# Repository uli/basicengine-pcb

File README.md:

#  BASIC Engine PCB

The BASIC Engine is a very low-cost single-board home computer with advanced 
2D color graphics and sound capabilities, roughly comparable to late-1980s
or early-1990s computers and video game consoles.  It can be built at home
without special skills or tools and using readily available components for
under 10 Euros in parts, or mass-produced for even less.

This repository contains KiCAD schematics and the PCB layout. Gerber files
for ordering PCBs can be found in the [release section](https://github.com/uli/basicengine-pcb/releases).

Software can be found in the [BASIC Engine firmware](https://github.com/uli/basicengine-firmware)
repository.

## Hardware features

- ESP12-E/F module with ESP8266 SoC and 4 MB flash memory
- VS23S010 video controller with 128k RAM and composite video output in PAL or NTSC
- 5-bit PCM sound from I2S controller
- MicroSD card slot
- PS/2 and PS/2-compatible USB keyboard interface
- PlayStation controller port
- PCF8575 I/O extender with 16 GPIO pins
- I2C and SPI busses on I/O expansion connector
- power supplied via Micro-USB socket or pin header
- RCA connectors for video and audio

## Components

The BASIC Engine does not use any obsolete components that may be difficult
to obtain.  Nevertheless, you will have to put in at least three orders to
get all required parts.

I would recommend to get the circuit board from JLCPCB or Smart Prototyping,
the VS23S010D-L chip from TME, and all other parts from AliExpress.  AE
usually has the lowest price, and this project is all about the cheap.

You will usually have to order more components than you actually intend to
use, because
- they are only offered in larger quantities,
- you may want to save on shipping in case you decide to build more BASIC Engines,
- you are likely to break or lose a few parts while building the device, or
- all of the above.

**Note:** Unless noted otherwise, all links lead to suppliers and components
I have bought myself in the past and that have received the "Good Enough for
BASIC Engine" seal of approval.  Nevertheless you **order at your own
risk**, and I cannot be held responsible for the quality of the services or
products provided to you.  I am not affiliated with any of the linked
suppliers.

### Required components

|Qty	|Name				|Package|Where to get it					|Links|
|-------|-------------------------------|-------|-------------------------------------------------------|-----|
|1	|Circuit Board			|	|Any board house					|[JLCPCB](https://jlcpcb.com/quote), [Smart Prototyping](https://www.smart-prototyping.com/PCB-Prototyping.html).
|1	|VS23S010D-L video controller	|	|TME (small quantities), VLSI (for large orders)	|[TME](https://www.tme.eu/en/details/vs23s010d-l/parallel-sram-memories-integ-circ/vlsi/), [VLSI](https://webstore.vlsi.fi/epages/vlsi.sf/en_GB/?ObjectPath=/Shops/2015020901/Categories/%22Circuits%20and%20KITs%22/VS23S010)
|1	|ESP-12F or ESP-12E microcontroller module|	|AliExpress, eBay, Amazon, various smaller retailers	|AliExpress: [1](https://www.aliexpress.com/item/New-version-ESP-12E-replace-ESP-12-ESP8266-remote-serial-Port-WIFI-wireless-module/32339917567.html), [2](https://www.aliexpress.com/item/1PCS-ESP-12F-ESP-12E-upgrade-ESP8266-Remote-Serial-Port-WIFI-Wireless-Module-ESP8266-4M-Flash/32521015580.html), [3](https://www.aliexpress.com/item/1PCS-ESP-12F-ESP-12E-upgrade-ESP8266-Remote-Serial-Port-WIFI-Wireless-Module-ESP8266-4M-Flash/32521015580.html)
|8	|Resistor 10K			|1206	|Generic part						|AliExpress: [1](https://www.aliexpress.com/item/500pcs-1206-SMD-Resistor-1-10K-ohm-chip-resistor-0-25W-1-4W-103/32806664929.html), [2](https://www.aliexpress.com/item/1206-10K-ohm-5-1-4W-Resistor-3216-103-Chip-resistor-500Pcs-Lot/32601535320.html)
|1	|Resistor 1M			|1206	|Generic part						|AliExpress: [1](https://www.aliexpress.com/item/500pcs-1206-SMD-Resistor-1-1M-ohm-chip-resistor-0-25W-1-4W-106/32806720513.html)
|1	|Resistor 75 Ohms		|1206	|Generic part						|AliExpress: [1](https://www.aliexpress.com/item/100pcs-lot-1206-5-75-ohm-75R-750-1-4W-0-25W-SMD-Resistor-3-2/32681304598.html), [2 (untested supplier)](https://www.aliexpress.com/item/200pcs-lot-SMD-Chip-Resistor-1206-68R-75R-82R-91R-100R-5-Resistance-68-75-82/32830700367.html)
|2	|Resistor 1K			|1206	|Generic part						|AliExpress: [1](https://www.aliexpress.com/item/500pcs-1206-SMD-Resistor-1-1K-ohm-chip-resistor-0-25W-1-4W-102/32806736163.html)
|8	|Capacitor 100nF		|1206	|Generic part						|AliExpress: [1](https://www.aliexpress.com/item/100pcs-100NF-X7R-Error-10-50V-0-1UF-104-1206-smd-capacitor/32810080501.html), [2](https://www.aliexpress.com/item/100PCS-SMD-chip-Ceramic-capacitors-1206-104-100NF-0-1UF-1206-Y5V/1478483210.html), [3](https://www.aliexpress.com/item/100PCS-1206-104-100NF-0-1UF-1206-SMD-capacitance/32836586837.html), [4](https://www.aliexpress.com/item/Free-Shipping-100PCS-1206-104-100NF-0-1UF-1206-SMD-capacitance/1096160798.html)
|2	|Capacitor 56pF			|1206	|Generic part						|AliExpress: [1](https://www.aliexpress.com/item/100pcs-1206-smd-capacitor-25pF-27pF-30pF-33pF-36pF-39pF-47pF-51pF-56pF-68pF/32832398866.html)
|1	|Electrolytic capacitor 10uF (**Revision 1 board only!**)	|THT	|Generic part		|AliExpress: [1](https://www.aliexpress.com/item/Free-shiiping-50pcs-Aluminum-electrolytic-capacitor-10uF-50V-5-7-Electrolytic-capacitor/32326606304.html), [2](https://www.aliexpress.com/item/50-pcs-Electrolytic-Capacitors-50V-10UF-4X7MM-Aluminum-Electrolytic-Capacitor/1808204181.html)
|2	|Electrolytic Capacitor 220uF (**Revision 1 board only!**)	|THT	|Generic part		|AliExpress: [1](https://www.aliexpress.com/item/1LOT-50PCS-Aluminum-Capacitors-220uF-227-20-6-11mm-25V-220000nF-220000000pF-Diameter6mm/32707926097.html)
|1	|Capacitor 10uF (**Revision 2 board only!**)|1206	|Generic part				|AliExpress: [1](https://www.aliexpress.com/item/Free-Shopping-100PCS-smd-ceramic-capacitor-1206-3216-10uf-106-25V-10/870636274.html), [2](https://www.aliexpress.com/store/product/100PCS-LOT-10uf-Error-10-50V-106-10UF-1206-SMD-Thick-Film-Chip-Multilayer-Ceramic-Capacitor/1815642_32818359105.html)
|2	|Capacitor 22uF (**Revision 2 board only!**)|1206	|Generic part				|AliExpress: [1](https://www.aliexpress.com/item/1206-22UF-226M-Y5V-10V-SMD-Chip-Multilayer-Ceramic-Capacitor-Capacitor/32506900002.html), [2](https://www.aliexpress.com/item/100PCS-LOT-22uf-Error-10-50V-226-22UF-1206-SMD-Thick-Film-Chip-Multilayer-Ceramic-Capacitor/32818355106.html)
|2	|RCA connectors			|THT	|Generic, but often overpriced part			|AliExpress: [1 (untested supplier)](https://www.aliexpress.com/item/ROHS-high-quality-one-pin-rca-jack-connector-RCA-103P/32305697673.html); no longer available: [red](https://www.aliexpress.com/item/10-Pcs-Pcb-Mount-3-Pin-Av-Concentric-Outlet-1-Rca-Female-Socket-Board-Connector/32778665156.html), [yellow](https://www.aliexpress.com/item/20-Pcs-3P-Pcb-Mounting-Yellow-1-Rca-Female-Outlet-Jack-Audio-Video-Av-Connector/32773151735.html)
|1	|Micro-USB connector		|SMT	|Generic, but often overpriced part			|AliExpress: [1](https://www.aliexpress.com/item/10Pcs-Micro-USB-5P-5-pin-Micro-USB-Jack-5Pins-No-Curling-Micro-USB-Connector-Tail/32697562974.html), [2](https://www.aliexpress.com/item/10pcs-LOT-Micro-USB-5P-5-pin-Micro-USB-Jack-5Pins-Micro-USB-Connector-Tail-Charging/32482316889.html), [3](https://www.aliexpress.com/item/10pcs-G21-Micro-USB-5pin-DIP-Female-Connector-For-Mobile-Phone-Mini-USB-Charging-Socket-Curly/32739335401.html), [4](https://www.aliexpress.com/item/50pcs-Lot-Micro-USB-5pin-B-type-Female-Connector-For-Mobile-Phone-Micro-USB-Jack-Connector/32740232877.html)
|1	|Regulator AMS1117 3.3V		|SOT-223|Generic, sometimes overpriced part			|AliExpress: [1](https://www.aliexpress.com/item/10pcs-AMS1117-3-3-AMS1117-LM1117-1117-3-3V-1A-Voltage-Regulator/32348815272.html); eBay DE: [1](https://www.ebay.de/itm/50-Stueck-AMS1117-3-3-Niedrig-Aussetzer-Spannungsregler-3-3V-1A-SOT-223-GY-/262752156305?hash=item3d2d3fba91)
|1	|74HC04 hex inverter		|SOIC-14|Generic part						|AliExpress: [1](https://www.aliexpress.com/item/20PCS-74HC04D-SOP14-74HC04-SOP-SN74HC04DR-SMD-new-and-original-IC-free-shipping/32545540311.html), [2](https://www.aliexpress.com/item/20PCS-74HC04-SOP/32833871593.html)
|1	|Crystal 3.579545 MHz (NTSC) or 4.433619 MHz (PAL)|HC49-S	|Generic part				|AliExpress: [NTSC](https://www.aliexpress.com/item/10pcs-lot-Crystal-Oscillator-3-579545MHz-3-579545-MHz3-579545M-Hz-3-579545M-Mini-Passive-Resonator/32674141136.html), [PAL (untested supplier)](https://www.aliexpress.com/item/4-433MHZ-4-433M-HC-49S-Quartz-crystal-4-433Mhz-4-433m-DIP-Quartz-crystal-resonators/897579150.html)
|1	|PS/2 keyboard connector (female)|THT	|AliExpress, some distributors				|AliExpress: [green](https://www.aliexpress.com/item/20PCS-Lot-PS2-Green-Plug-Jack-Socket-Connector-6Pin-for-keyboard-mouse/32502046263.html), [purple](https://www.aliexpress.com/item/20PCS-Lot-PS2-Purple-Plug-Jack-Socket-Connector-6P-6Pin-for-keyboard-mouse/32503500361.html)

### Not strictly required, but strongly recommended components

|Qty	|Name				|Package|Who can supply it					|Links|
|-------|-------------------------------|-------|-------------------------------------------------------|-----|
|1	|Pin header 1x7 (programming header)|	|Generic part						|AliExpress: [1](https://www.aliexpress.com/item/1-pcs-color-2-54mm-Black-White-Red-Yellow-Blue-Green-1X40-Single-Row-Pin-Male/32776690848.html) (1x40 headers, cut them to size)
|1	|MicroSD socket			|SMT	|AliExpress, eBay					|AliExpress: [1](https://www.aliexpress.com/item/10pcs-MicroSD-Card-socket-connector-pop-up/1878206296.html), [2](https://www.aliexpress.com/item/Free-Shipping-10PCS-MicroSD-Card-socket-connector-pop-up/1688131297.html); eBay DE: [1](https://www.ebay.de/itm/10Pcs-TransFlash-SD-TF-Micro-Memory-Card-Self-eject-Socket-Adapter-Plug-NEW-/272247684402?hash=item3f6339fd32)
|1	|Push button 6x6x4.3 mm		|THT	|Generic part						|AliExpress: [1](https://www.aliexpress.com/item/10PCS-TC-1212T-6x6x4-3-mm-Tact-Tactile-Push-Button-Momentary-SMD-PCB-Switch/32633194631.html), [2](https://www.aliexpress.com/item/20PCS-6X6X4-3-DIP-vertical-Tactile-Tact-Push-Button-Switch-Micro-Switch-Momentary-6-6-4/32628754816.html)
|1	|PCF8575TS I2C I/O extender	|SSOP-24|Generic part; AliExpress recommended for price		|AliExpress: [1](https://www.aliexpress.com/item/5PCS-PCF8575TS-SSOP24-PCF8575-SOP24/32836090166.html)
|1	|Raspberry Pi 3 case		|	|Generic part						|AliExpress: [1](https://www.aliexpress.com/item/case-H1-Black-Raspberry-PI-3-model-B-Case-Cover-Shell-Enclosure-ABS-Plastic-Box-for/32813179636.html), [2](https://www.aliexpress.com/item/box-F3-for-Raspberry-PI-3-model-B-Transparent-Green-Case-Cover-Shell-Enclosure-Box/32824924648.html), [3](https://www.aliexpress.com/item/10pcs-lot-Raspberry-Pi-3-case-Official-ABS-enclosure/32816503175.html), [4](https://www.aliexpress.com/item/New-Arrival-Raspberry-Pi-3-Model-B-Case-Black-Red-ABS-Plastic-Box-Closed-Cover-Shell/32716194619.html), [5](https://www.aliexpress.com/item/Raspberry-Pi-3-Model-B-ABS-Case-Black-White-Tranparent-ABS-Enclosure-Box-Shell-for-Raspberry/32651704900.html)

### Optional components

|Qty	|Name				|Package|Who can supply it					|Links|
|-------|-------------------------------|-------|-------------------------------------------------------|-----|
|1	|Pin header 1x3 pins (alternative power supply)|	|AliExpress recommended for price	|see "Pin header 1x7"
|1	|USB A connector (alternative keyboard connector)|THT	|Generic part				|AliExpress: [1](https://www.aliexpress.com/item/10-PCS-USB-Type-A-Female-PCB-Mount-Socket-Plug-Connector-Right-Angle-4-Pin-New/32821630374.html), [2](https://www.aliexpress.com/item/10PCS-USB-type-A-USB-mother-Curved-needle/32265708803.html)
|1	|Pin header 2x20 pins (expansion connector)|	|AliExpress recommended for price		|AliExpress: [1](https://www.aliexpress.com/item/30-pcs-set-2-54mm-Black-White-Red-Yellow-Blue-Green-2X40-Double-Row-Pin-Male/32776804458.html) (2x40 headers, cut them in half)
|1	|PlayStation controller connector (female)|	|AliExpress					|AliExpress: [1](https://www.aliexpress.com/item/10pcs-wholesale-Replacement-9-Pin-Female-Connector-Game-Controller-Socket-Slot-for-PS2-Console-for-playstation/32769355434.html), [2](https://www.aliexpress.com/item/10pcs-Replacement-9-Pin-90-degrees-Female-Connector-Game-Controller-Socket-Slot-for-PS2-Console/32818887920.html)

### Programming tools

Used to flash the firmware into the microcontroller module. You only need one set of these.

|Qty	|Name				|Package|Who can supply it				|Links|
|-------|-------------------------------|-------|-----------------------------------------------|-----|
|1	|USB-to-serial converter	|	|AliExpress, eBay				|AliExpress: [1](https://www.aliexpress.com/item/1pcs-FT232RL-FTDI-USB-3-3V-5-5V-to-TTL-Serial-Adapter-Module-forArduino-Mini-Port/32650148276.html), [2](https://www.aliexpress.com/item/CP2102-USB-2-0-to-TTL-UART-Module-6Pin-Serial-Converter-STC-Replace-FT232-Module/32279672853.html)
|7	|Dupont wires female/female (for wiring the converter to the programming header)|	|AliExpress, eBay	|AliExpress: [1 (untested supplier)](https://www.aliexpress.com/item/40pcs-dupont-cable-jumper-wire-dupont-line-female-to-female-dupont-line-20cm-1P-40P-free/32848338475.html), [2 (untested supplier)](https://www.aliexpress.com/item/40pcs-dupont-cable-jumper-wire-dupont-line-female-to-female-dupont-line-20cm-1P-1P-for/32586620163.html)

## Ordering the PCB

If you have never had a custom circuit board made, you may find the
multitude of options you are presented with on the board house's ordering
page confusing.  The good news is that you do not have to worry about most
of them, because they have been set to reasonable defaults already.  If you
order with JLCPCB or Smart Prototyping using the links above, all you have
to do is upload the ZIP file containing the Gerber files that you can find
in the [release section](https://github.com/uli/basicengine-pcb/releases)
and specify the dimensions of the board (85x56 mm).  All other options can
be left as is.

(Just to be on safe side: At the time of writing these options were: 2
layers, 1.6 mm thickness, HASL with lead, 1oz copper weight, material FR4.)

## Assembling the BASIC Engine

Even though it uses some small-pitch components, the BASIC Engine has been
designed to be easy to assemble.

Click on the thumbnail below to watch a one-hour silent video showing how to
build it using a soldering iron, a heat gun, tweezers,
solder wire and side cutters, without fancy tools, mad soldering skills and
with only a minimal amount of patience:

## PCB Errata

Revision 2 of the PCB contains one error:

- R6 value is given as "22R", should be "75R".

Revision 1 of the PCB contains two errors:

- R6 value is given as "22R", should be "75R".
- C3 and C4 values are given as "10p", should be "56p".

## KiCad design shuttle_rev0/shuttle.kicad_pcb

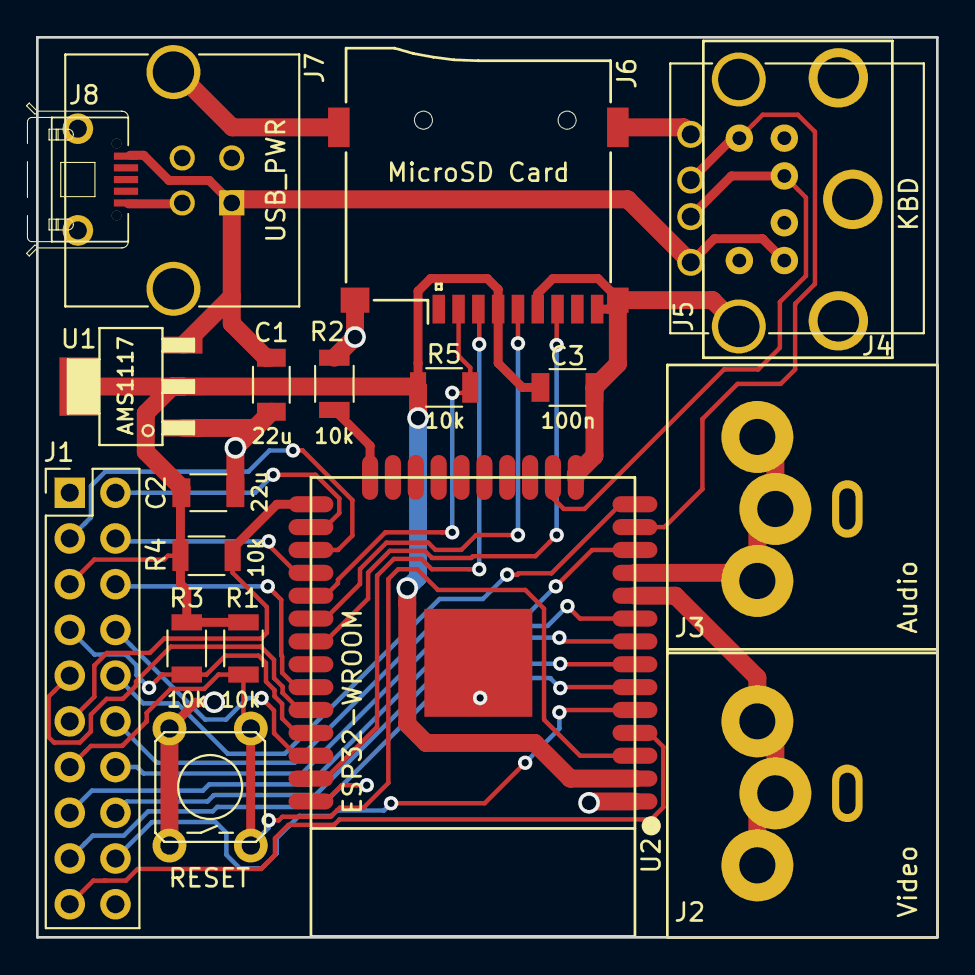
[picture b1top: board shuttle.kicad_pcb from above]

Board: 2 copper layers, 50.0 x 50.0 mm, 19 parts (0 on the bottom side), 29 nets.

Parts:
C1, C2: 22u; C_1206
C3: 100n; C_1206
J1: EXP; Pin_Header_Straight_2x10_Pitch2.54mm
J2: Video; rca_uni
J3: Audio; rca_uni
J4: PS2_KBD; MINI-DIN-6-FULL-SHIELD
J5: KBD; USB_A
J6: MicroSD Card; Conn_uSDcard
J7: USB_PWR; USB_B_MUSB_Straight
J8: USB_PWR_U; AB2_USB_MICRO_SMD
R1, R2, R3, R4, R5: 10k; R_1206
SW1: RESET; AB2_PB_MOM_6MM_PTH_BLK
U1: AMS1117; AB2_SOT223
U2: ESP32-WROOM

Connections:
+5V: C1.1, J4.4, J5.1, J7.1, J8.1, U1.3
/3V3: C2.1, C3.1, J1.5, J6.4, R1.2, R3.1, R4.1, R5.1, U1.2, U2.2
/AUDIO: J3.1, U2.11
/DBG_DTR: J1.11, R4.2, U2.25
/DBG_RX: J1.9, U2.34
/DBG_TX: J1.7, R3.2, U2.35
/EN: J1.13, R1.1, SW1.2, U2.3
/GPIO2: R2.1, U2.24
/GPIO4: J1.2, U2.26
/GPIO12: J1.10, U2.14
/GPIO16: J1.3, U2.27
/GPIO17: J1.4, U2.28
/GPIO21: J1.6, U2.33
/GPIO22: J1.8, U2.36
/GPIO27: J1.12, U2.12
/GPIO32: J1.15, U2.8
/GPIO33: J1.14, U2.9
/GPIO34: J1.17, U2.6
/GPIO35: J1.16, U2.7
/MISO: J6.7, U2.31
/MOSI: J6.3, U2.37
/PS2CLK: J4.5, J5.3, U2.13
/PS2DAT: J4.1, J5.2, U2.16
/SCLK: J6.5, U2.30
/SDCS: J6.2, R5.2, U2.29
/SENSOR_VN: J1.18, U2.5
/SENSOR_VP: J1.19, U2.4
/VIDEO: J2.1, U2.10
GND: C1.2, C2.2, C3.2, J1.1, J1.20, J2.2, J3.2, J4.3, J5.4, J5.5, J6.6, J6.9, J7.4, J7.5, J8.5, R2.2, SW1.1, U1.1, U2.1, U2.15, U2.38, U2.39

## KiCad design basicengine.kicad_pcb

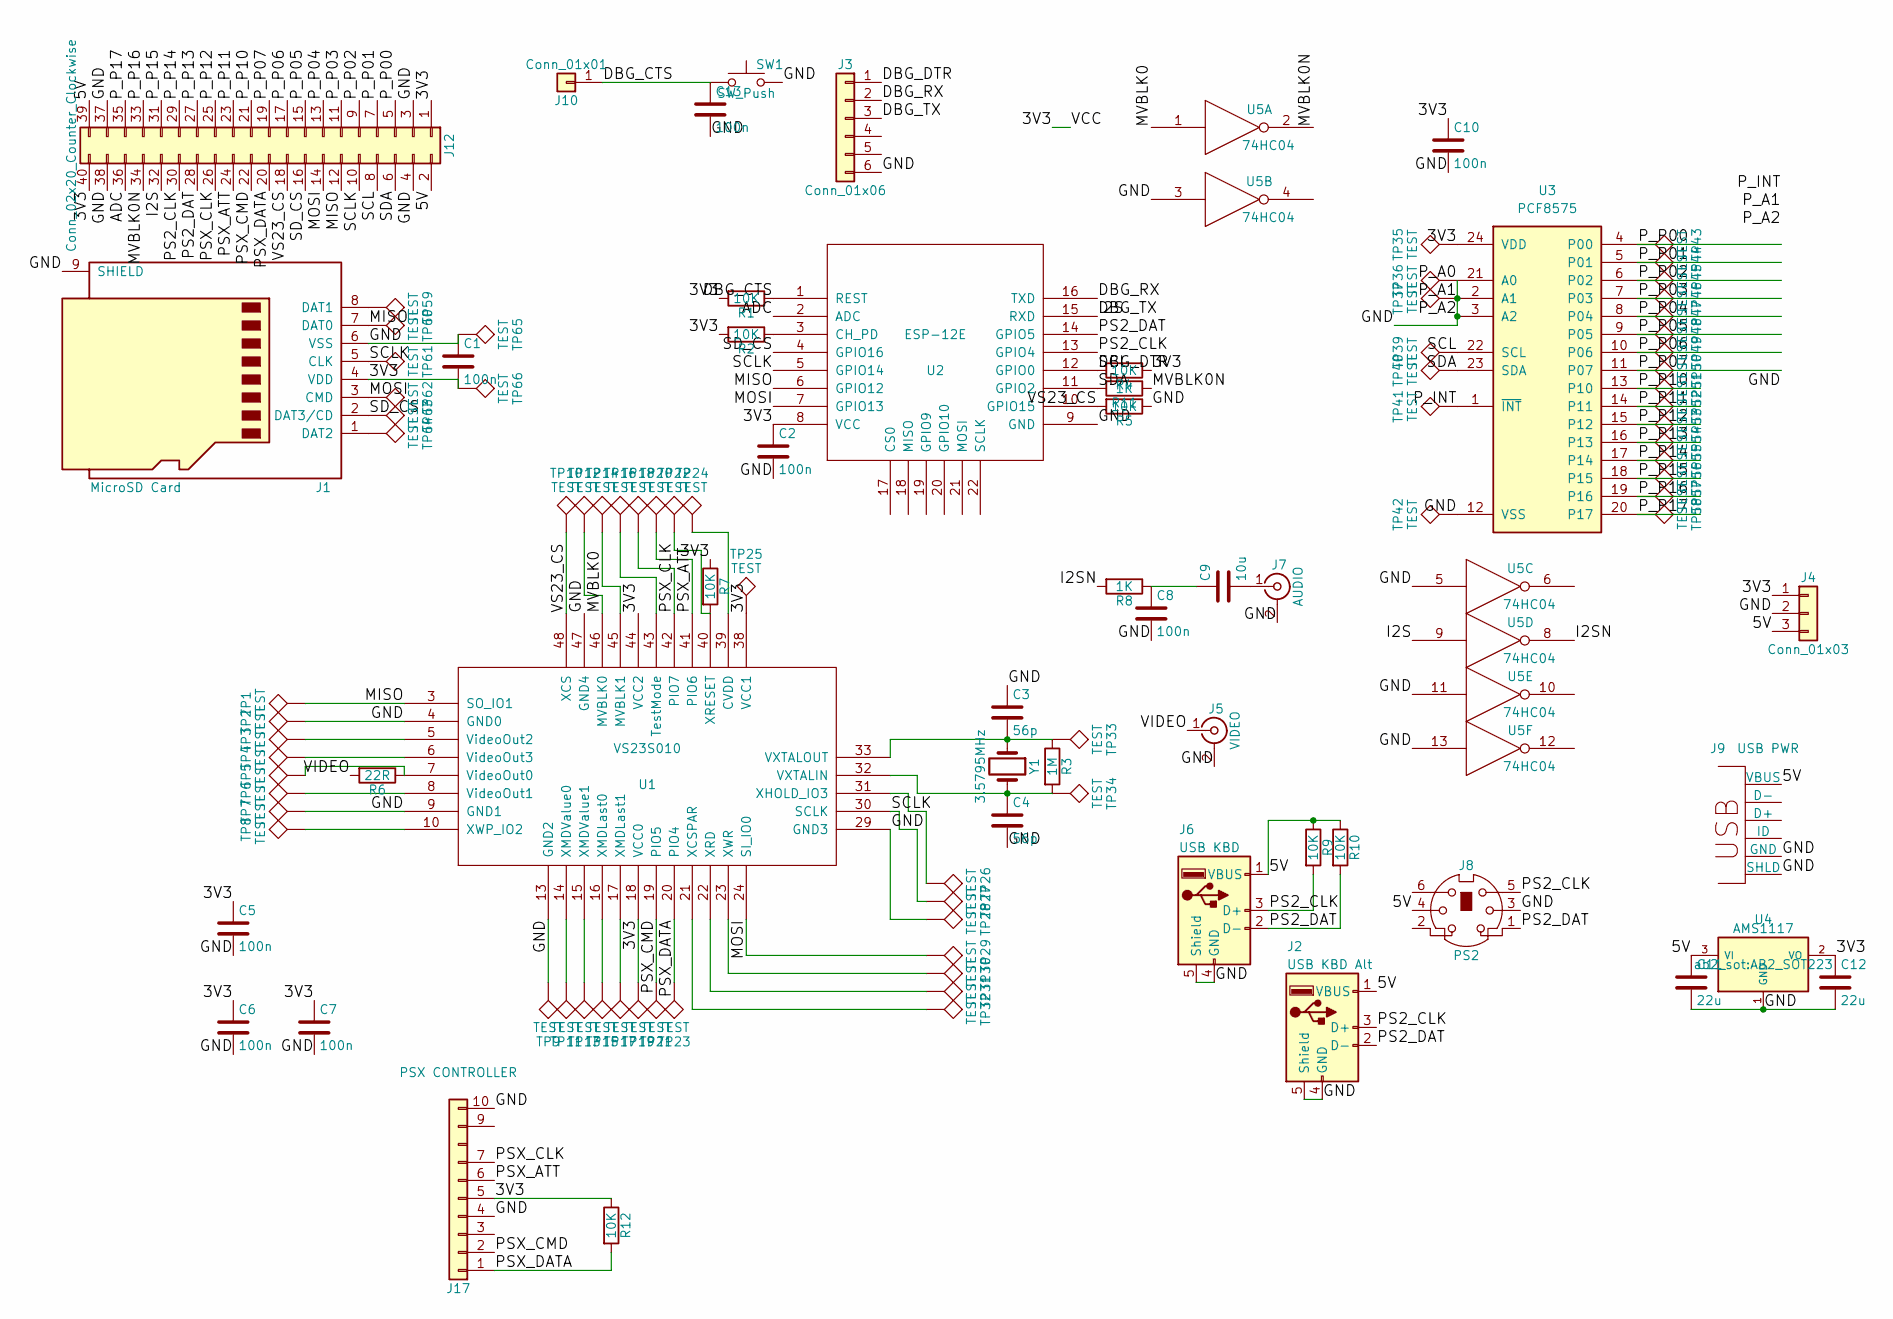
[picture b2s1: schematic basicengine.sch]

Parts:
C1, C2, C5, C6, C7, C8, C10, C13: 100n; C_1206_HandSoldering
C3, C4: 56p; C_1206_HandSoldering
C9: 10u; C_1206_HandSoldering
C11, C12: 22u; C_1206_HandSoldering
J1: MicroSD Card; Conn_uSDcard
J2: USB KBD Alt; USB_A
J3: Conn_01x06; Pin_Header_Straight_1x06
J4: Conn_01x03; Pin_Header_Straight_1x03
J5: VIDEO; rca
J6: USB KBD; USB_A
J7: AUDIO; rca
J8: PS2; MINI-DIN-6-FULL-SHIELD
J9: USB PWR; AB2_USB_MICRO_SMD
J10: Conn_01x01; Pin_Header_Straight_1x01
J12: Conn_02x20_Counter_Clockwise; Pin_Header_Straight_2x20
J17: PSX CONTROLLER; psx-con-female
R1, R2, R4, R5, R7, R9, R10, R12: 10K; R_1206_HandSoldering
R3: 1M; R_1206_HandSoldering
R6: 22R; R_1206_HandSoldering
R8, R11: 1K; R_1206_HandSoldering
SW1: SW_Push; AB2_PB_MOM_6MM_PTH_BLK
TP1, TP2, TP3, TP4, TP5, TP6, TP7, TP8, TP9, TP10, TP11, TP12, TP13, TP14, TP15, TP16, TP17, TP18, TP19, TP20, TP21, TP22, TP23, TP24, TP25, TP26, TP27, TP28, TP29, TP30, TP31, TP32, TP33, TP34, TP35, TP36, TP37, TP39, TP40, TP41, TP42, TP43, TP44, TP45, TP46, TP47, TP48, TP49, TP50, TP51, TP52, TP53, TP54, TP55, TP56, TP57, TP58, TP59, TP60, TP61, TP62, TP63, TP64, TP65, TP66: TEST; Measurement_Point_Round-SMD-Pad_Small
U1: VS23S010; LQFP-48_7x7mm_Pitch0.5mm
U2: ESP-12E; ESP-12E_SMD
U3: PCF8575; SSOP-24_5.3x8.2mm_Pitch0.65mm; MPN PCF8575TS/1,112
U4: AMS1117; AB2_SOT223
U5: 74HC04; SOIC-14_3.9x8.7mm_Pitch1.27mm
Y1: 3.5795MHz; Crystal_HC49-U_Vertical

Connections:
/5V: C11.1, J2.1 (VBUS), J4.3, J6.1 (VBUS), J8.4, J9.1 (VBUS), J12.2, J12.39, R9.1, R10.1, U4.3 (VI)
/ADC: J12.36, U2.2 (ADC)
/DBG_CTS: C13.1, J10.1, R1.1, SW1.1, U2.1 (REST)
/DBG_DTR: J3.1, J12.8, R4.2, TP39.1, U2.12 (GPIO0), U3.22 (SCL)
/DBG_RX: J3.2, U2.16 (TXD)
/DBG_TX: J3.3, J12.32, U2.15 (RXD), U5.9
/I2SN: R8.2, U5.8
/MISO: J1.7 (DAT0), J12.12, TP1.1, TP60.1, U1.3 (SO_IO1), U2.6 (GPIO12)
/MOSI: J1.3 (CMD), J12.14, TP29.1, TP62.1, U1.24 (SI_IO0), U2.7 (GPIO13)
/MVBLK0: TP12.1, U1.46 (MVBLK0), U5.1
/MVBLK0N: J12.34, R11.1, U5.2
/PS2_CLK: J2.3 (D+), J6.3 (D+), J8.5, J12.30, R9.2, U2.13 (GPIO4)
/PS2_DAT: J2.2 (D-), J6.2 (D-), J8.1, J12.28, R10.2, U2.14 (GPIO5)
/PSX_ATT: J12.24, J17.6, TP20.1, U1.41 (PIO6)
/PSX_CLK: J12.26, J17.7, TP18.1, U1.42 (PIO7)
/PSX_CMD: J12.22, J17.2, TP21.1, U1.19 (PIO5)
/PSX_DATA: J12.20, J17.1, R12.2, TP23.1, U1.20 (PIO4)
/P_INT: TP41.1, U3.1 (~INT)
/P_P00: J12.5, TP43.1, U3.4 (P00)
/P_P01: J12.7, TP44.1, U3.5 (P01)
/P_P02: J12.9, TP45.1, U3.6 (P02)
/P_P03: J12.11, TP46.1, U3.7 (P03)
/P_P04: J12.13, TP47.1, U3.8 (P04)
/P_P05: J12.15, TP48.1, U3.9 (P05)
/P_P06: J12.17, TP49.1, U3.10 (P06)
/P_P07: J12.19, TP50.1, U3.11 (P07)
/P_P10: J12.21, TP51.1, U3.13 (P10)
/P_P11: J12.23, TP52.1, U3.14 (P11)
/P_P12: J12.25, TP53.1, U3.15 (P12)
/P_P13: J12.27, TP54.1, U3.16 (P13)
/P_P14: J12.29, TP55.1, U3.17 (P14)
/P_P15: J12.31, TP56.1, U3.18 (P15)
/P_P16: J12.33, TP57.1, U3.19 (P16)
/P_P17: J12.35, TP58.1, U3.20 (P17)
/SCLK: J1.5 (CLK), J12.10, TP27.1, TP61.1, U1.30 (SCLK), U2.5 (GPIO14)
/SDA: J12.6, R11.2, TP40.1, U2.11 (GPIO2), U3.23 (SDA)
/SD_CS: J1.2 (DAT3/CD), J12.16, TP63.1, U2.4 (GPIO16)
/VIDEO: J5.1 (In), R6.2
/VS23_CS: J12.18, R5.2, TP10.1, U1.48 (XCS), U2.10 (GPIO15)
GND: C1.1, C2.2, C3.1, C4.2, C5.2, C6.2, C7.2, C8.2, C10.2, C11.2, C12.2, C13.2, J1.6 (VSS), J1.9 (SHIELD), J2.4 (GND), J2.5 (Shield), J3.6, J4.2, J5.2 (Ext), J6.4 (GND), J6.5 (Shield), J7.2 (Ext), J8.3, J9.5 (GND), J9.SH (SHLD), J12.3, J12.4, J12.37, J12.38, J17.4, J17.10, R5.1, SW1.2, TP2.1, TP7.1, TP9.1, TP28.1, TP36.1, TP37.1, TP42.1, TP65.1, U1.4 (GND0), U1.9 (GND1), U1.13 (GND2), U1.29 (GND3), U1.47 (GND4), U2.9 (GND), U3.2 (A1), U3.3 (A2), U3.12 (VSS), U3.21 (A0), U4.1 (GND), U5.3, U5.5, U5.7 (GND), U5.11, U5.13
unnamed: C3.2, R3.1, TP33.1, U1.33 (VXTALOUT), Y1.1
unnamed: C4.1, R3.2, TP34.1, U1.32 (VXTALIN), Y1.2
unnamed: C8.1, C9.1, R8.1
unnamed: C9.2, J7.1 (In)
unnamed: J1.1 (DAT2), TP64.1
unnamed: J1.8 (DAT1), TP59.1
unnamed: R2.1, U2.3 (CH_PD)
unnamed: R6.1, TP5.1, U1.7 (VideoOut0)
unnamed: R7.2, TP22.1, U1.40 (XRESET)
unnamed: TP3.1, U1.5 (VideoOut2)
unnamed: TP4.1, U1.6 (VideoOut3)
unnamed: TP6.1, U1.8 (VideoOut1)
unnamed: TP8.1, U1.10 (XWP_IO2)
unnamed: TP11.1, U1.14 (XMDValue0)
unnamed: TP13.1, U1.15 (XMDValue1)
unnamed: TP14.1, U1.45 (MVBLK1)
unnamed: TP15.1, U1.16 (XMDLast0)
unnamed: TP16.1, U1.43 (TestMode)
unnamed: TP17.1, U1.17 (XMDLast1)
unnamed: TP24.1, U1.39 (CVDD)
unnamed: TP26.1, U1.31 (XHOLD_IO3)
unnamed: TP30.1, U1.23 (XWR)
unnamed: TP31.1, U1.22 (XRD)
unnamed: TP32.1, U1.21 (XCSPAR)
VCC: C1.2, C2.1, C5.1, C6.1, C7.1, C10.1, C12.1, J1.4 (VDD), J4.1, J12.1, J12.40, J17.5, R1.2, R2.2, R4.1, R7.1, R12.1, TP19.1, TP25.1, TP35.1, TP66.1, U1.18 (VCC0), U1.38 (VCC1), U1.44 (VCC2), U2.8 (VCC), U3.24 (VDD), U4.2 (VO), U5.14 (VCC)

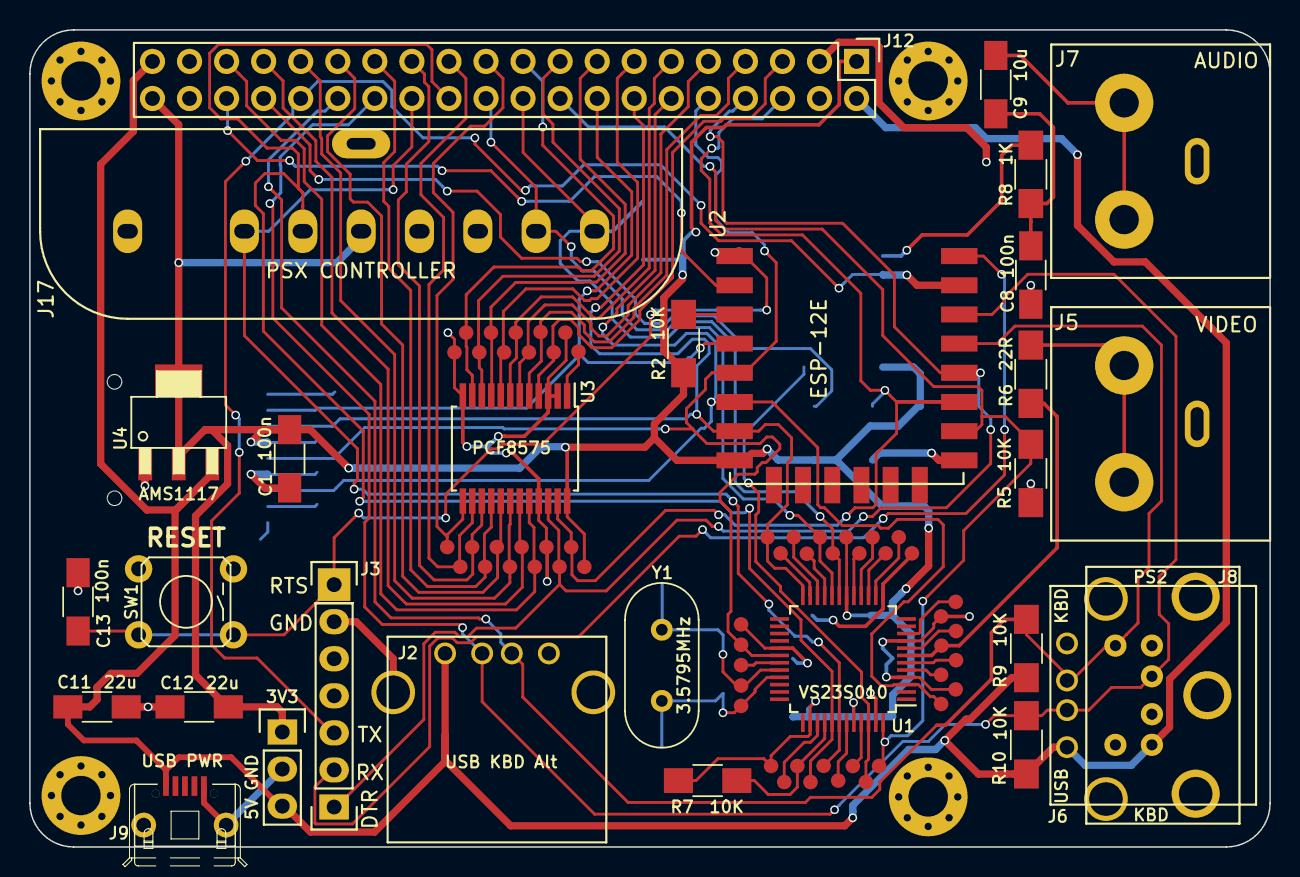
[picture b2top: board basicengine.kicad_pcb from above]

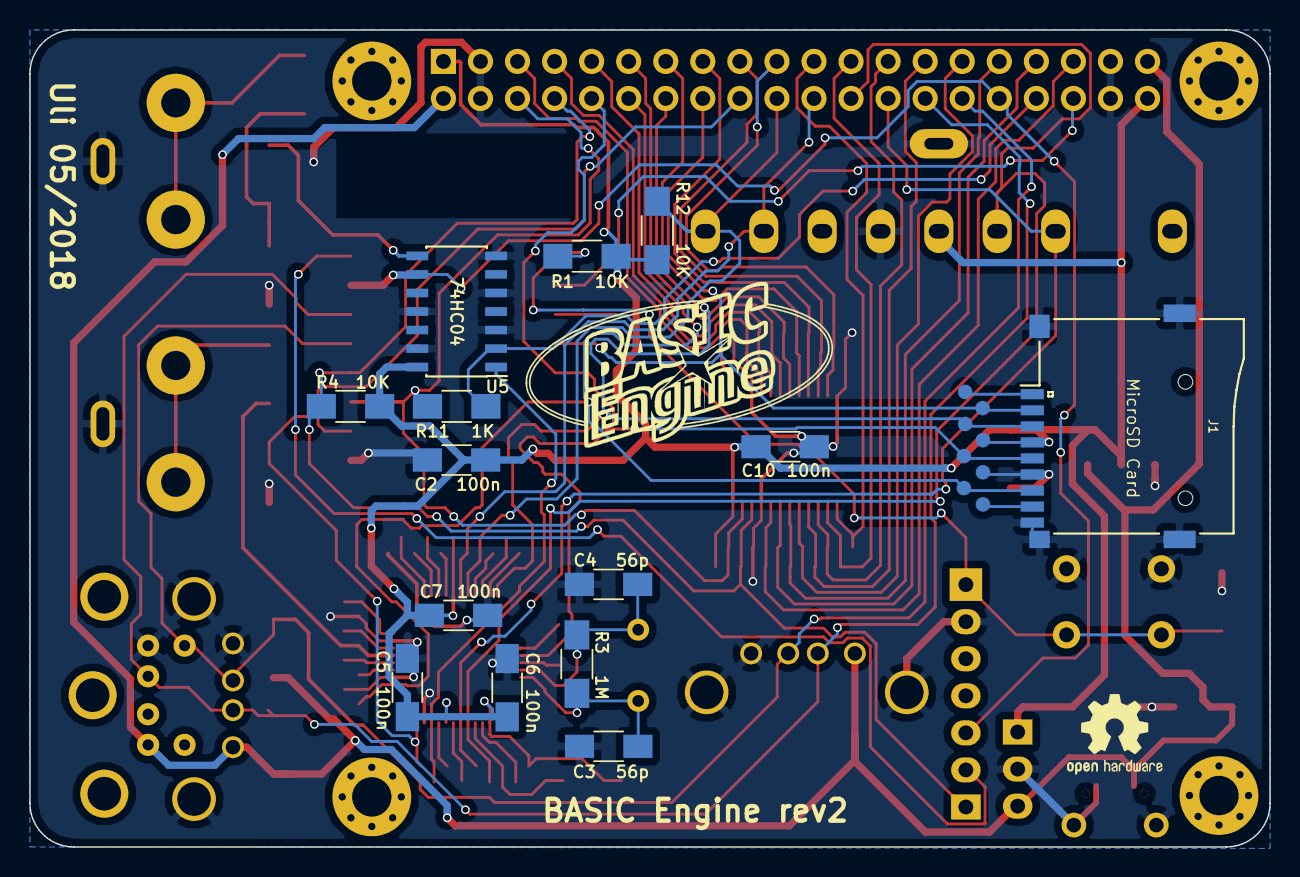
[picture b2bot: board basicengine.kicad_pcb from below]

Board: 2 copper layers, 85.0 x 56.0 mm, 109 parts (22 on the bottom side), 65 nets.

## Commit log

2018-04-28 import revision 1
2018-04-28 add image
2018-04-30 README.md: add component, assembly information, logo
2018-04-30 README.md: add rev1 errata
2018-05-07 sch: replace THT electrolytics with ceramic SMT caps
    Reduces regulator in/out capacitors from 220u to 22u; tested by writing
    data from network to SD card, seems to be stable.
2018-05-07 sch: change VS23S010 oscillator caps from 10p to 56p
    Yields more accurate color burst frequency, fixes B/W display on Sony
    KX-14CP1.
2018-05-07 pcb: add OSHW logo
2018-05-07 pcb: follow sch oscillator capacitor change from 10p to 56p
2018-05-07 pcb: revision 2
    - follow sch in replacing electrolytics with ceramic SMT caps
    - move J6 (primary USB KBD connector) left to reduce the proximity of
    its pads to the shielding of J8 (PS/2 connector)
    - move R9, R10 left to make space for J6
    - move BASIC Engine logo down a bit
    - update date and revision silkscreen
2018-06-02 README.md: add rev2 info
    - update parts links
    - add rev2 errata
2018-09-12 move BASIC Engine rev2 design to directory basicengine_rev2
2018-09-12 add BASIC Engine Shuttle rev0 design
